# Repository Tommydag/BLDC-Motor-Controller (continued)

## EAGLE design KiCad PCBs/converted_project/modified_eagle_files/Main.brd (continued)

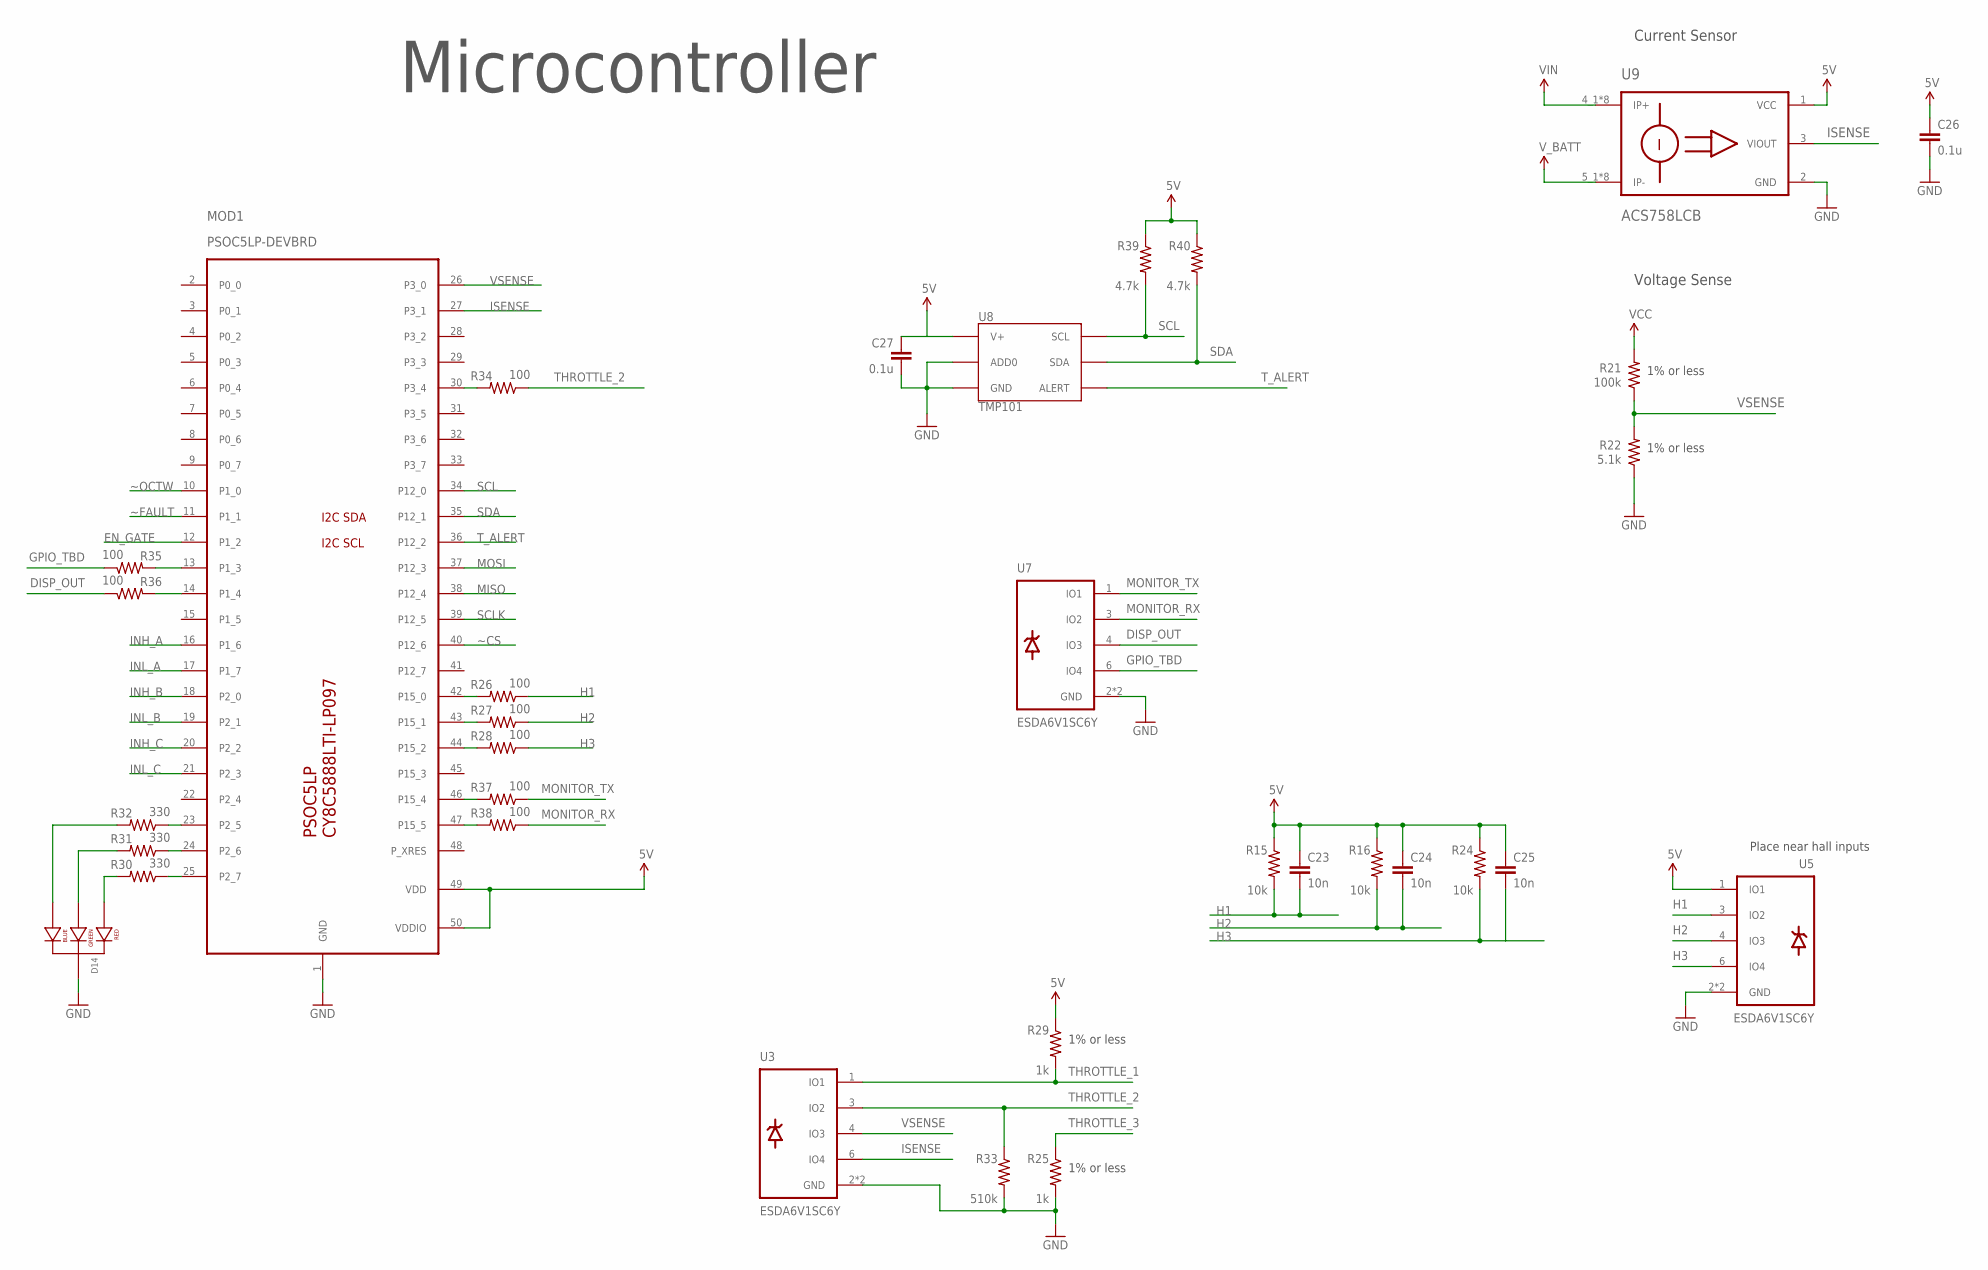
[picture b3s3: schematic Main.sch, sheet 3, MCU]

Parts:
C23, C24, C25: 10n; 0805
C26, C27: 0.1u; 0805
D14: LED-RGB-CC-THRUDIFFUSE; LED-RGB-THRU
MOD1: PSOC5LP-DEVBRD; TQFP100
R15, R16, R24: 10k; 0805
R21: 100k; 1206
R22: 5.1k; 1206
R25, R29: 1k; 0805
R26, R27, R28, R34, R35, R36, R37, R38: 100; 0805
R30, R31, R32: 330; 0805
R33: 510k; 0805
R39, R40: 4.7k; 0805
U3, U5, U7: ESDA6V1SC6Y; SOT23-6
U8: TMP101; SOT23-6
U9: ACS758LCB; CB5PIN

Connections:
5V: C23.1, C24.1, C25.1, C26.1, C27.1, R15.1, R16.1, R24.1, R29.1, R39.1, R40.1, U5.1 (IO1), U8.4 (V+), U9.1 (VCC); also elsewhere on the board
DISP_OUT: R36.1, U7.4 (IO3); also elsewhere on the board
EN_GATE: MOD1.12 (P1_2); also elsewhere on the board
GND: C26.2, C27.2, D14.2 (CATHODE), MOD1.1 (GND), R22.1, R25.2, R33.2, U3.2 (GND), U3.5 (GND), U5.2 (GND), U5.5 (GND), U7.2 (GND), U7.5 (GND), U8.2 (GND), U8.5 (ADD0), U9.2 (GND); also elsewhere on the board
GPIO_TBD: R35.1, U7.6 (IO4); also elsewhere on the board
H1: C23.2, R15.2, R26.1; also elsewhere on the board
H2: C24.2, R16.2, R27.1; also elsewhere on the board
H3: C25.2, R24.2, R28.1; also elsewhere on the board
ISENSE: MOD1.27 (P3_1), U3.6 (IO4), U9.3 (VIOUT)
MONITOR_RX: R38.1, U7.3 (IO2); also elsewhere on the board
MONITOR_TX: R37.1, U7.1 (IO1); also elsewhere on the board
unnamed: MOD1.42 (P15_0), R26.2
unnamed: MOD1.43 (P15_1), R27.2
unnamed: MOD1.44 (P15_2), R28.2
unnamed: MOD1.49 (VDD), MOD1.50 (VDDIO)
unnamed: MOD1.25 (P2_7), R30.1
unnamed: MOD1.24 (P2_6), R31.1
unnamed: MOD1.23 (P2_5), R32.1
unnamed: D14.1 (RED_CATHODE), R30.2
unnamed: D14.3 (GREEN_CATHODE), R31.2
unnamed: D14.4 (BLUE_CATHODE), R32.2
unnamed: MOD1.30 (P3_4), R34.2
unnamed: MOD1.14 (P1_4), R36.2
unnamed: MOD1.13 (P1_3), R35.2
unnamed: MOD1.46 (P15_4), R37.2
unnamed: MOD1.47 (P15_5), R38.2
SCL: MOD1.34 (P12_0), R39.2, U8.1 (SCL)
SDA: MOD1.35 (P12_1), R40.2, U8.6 (SDA)
THROTTLE_1: R29.2, U3.1 (IO1); also elsewhere on the board
THROTTLE_2: R33.1, R34.1, U3.3 (IO2); also elsewhere on the board
THROTTLE_3: R25.1; also elsewhere on the board
T_ALERT: MOD1.36 (P12_2), U8.3 (ALERT)
VCC: R21.2; also elsewhere on the board
VIN: U9.4_1 (IP+), U9.4_2 (IP+), U9.4_3 (IP+), U9.4_4 (IP+), U9.4_5 (IP+), U9.4_6 (IP+), U9.4_7 (IP+), U9.4_8 (IP+); also elsewhere on the board
VSENSE: MOD1.26 (P3_0), R21.1, R22.2, U3.4 (IO3)
V_BATT: U9.5_1 (IP-), U9.5_2 (IP-), U9.5_3 (IP-), U9.5_4 (IP-), U9.5_5 (IP-), U9.5_6 (IP-), U9.5_7 (IP-), U9.5_8 (IP-); also elsewhere on the board

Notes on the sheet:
Microcontroller
Current Sensor
Voltage Sense
Place near hall inputs
1% or less

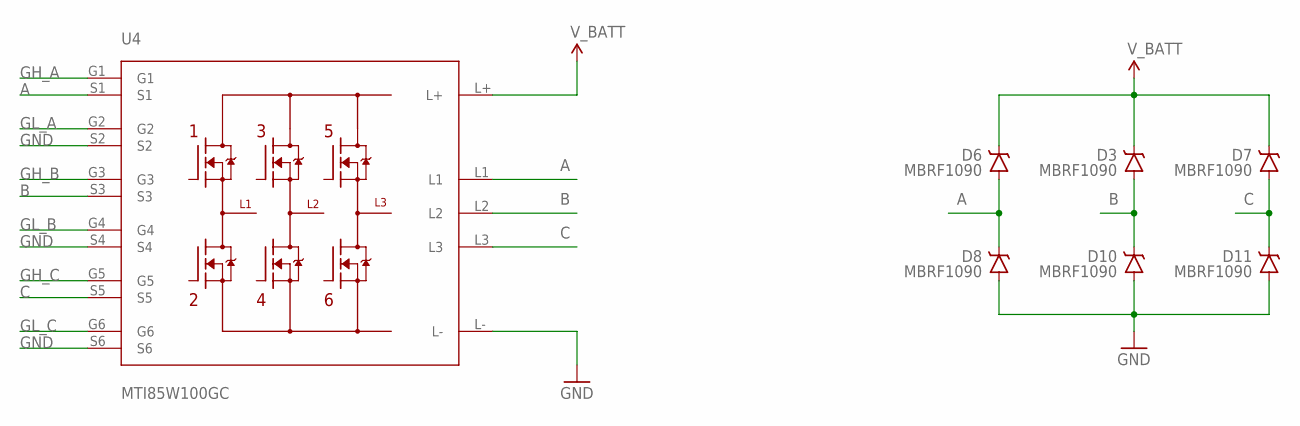
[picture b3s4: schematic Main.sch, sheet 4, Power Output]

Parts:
D3, D6, D7, D8, D10, D11: MBRF1090; TO-220H_2
U4: MTI85W100GC; ISOPLUS-DIL

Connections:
A: D6.2 (A), D8.1 (C), U4.L1, U4.S1; also elsewhere on the board
B: D3.2 (A), D10.1 (C), U4.L2, U4.S3; also elsewhere on the board
C: D7.2 (A), D11.1 (C), U4.L3, U4.S5; also elsewhere on the board
GH_A: U4.G1; also elsewhere on the board
GH_B: U4.G3; also elsewhere on the board
GH_C: U4.G5; also elsewhere on the board
GL_A: U4.G2; also elsewhere on the board
GL_B: U4.G4; also elsewhere on the board
GL_C: U4.G6; also elsewhere on the board
GND: D8.2 (A), D10.2 (A), D11.2 (A), U4.L-, U4.S2, U4.S4, U4.S6; also elsewhere on the board
V_BATT: D3.1 (C), D6.1 (C), D7.1 (C), U4.L+; also elsewhere on the board

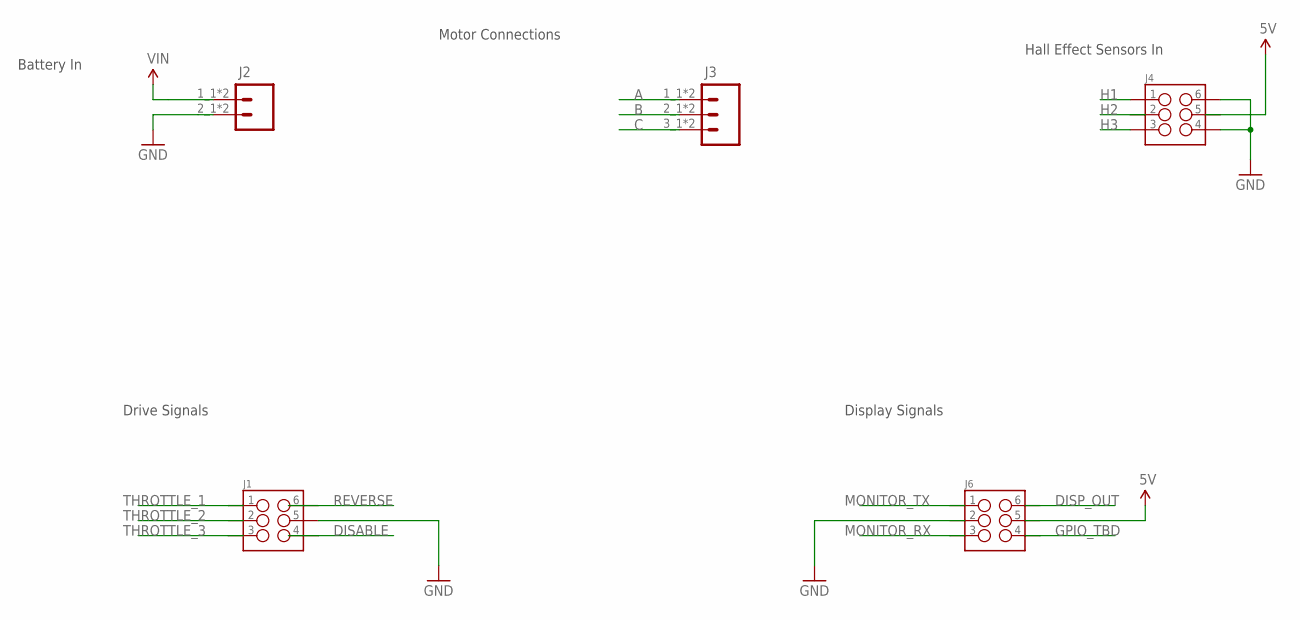
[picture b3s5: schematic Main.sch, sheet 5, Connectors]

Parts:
J1, J4, J6: M03X2MINIFIT_JR; 2X03_MINIFIT_JR
J2: M02MINIFIT-SR; MINIFIT_SR
J3: M03MINIFIT-SR3; MINIFIT-SRX3

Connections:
5V: J4.5, J6.5; also elsewhere on the board
A: J3.1_1 (1), J3.1_2 (1); also elsewhere on the board
B: J3.2_1 (2), J3.2_2 (2); also elsewhere on the board
C: J3.3_1 (3), J3.3_2 (3); also elsewhere on the board
DISABLE: J1.4
DISP_OUT: J6.6; also elsewhere on the board
GND: J2.2_1 (2), J2.2_2 (2), J4.4, J4.6, J6.2; also elsewhere on the board
GPIO_TBD: J6.4; also elsewhere on the board
H1: J4.1; also elsewhere on the board
H2: J4.2; also elsewhere on the board
H3: J4.3; also elsewhere on the board
MONITOR_RX: J6.3; also elsewhere on the board
MONITOR_TX: J6.1; also elsewhere on the board
REVERSE: J1.6
THROTTLE_1: J1.1; also elsewhere on the board
THROTTLE_2: J1.2; also elsewhere on the board
THROTTLE_3: J1.3; also elsewhere on the board
VIN: J2.1_1 (1), J2.1_2 (1); also elsewhere on the board

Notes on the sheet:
Hall Effect Sensors In
Battery In
Drive Signals
Motor Connections
Display Signals

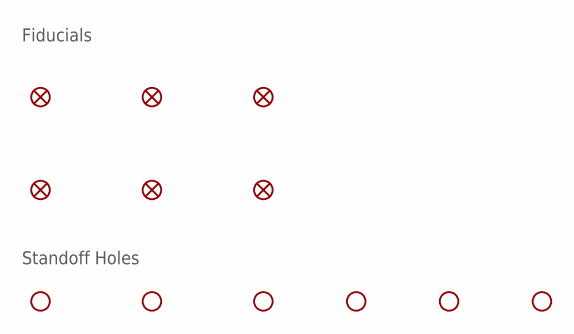
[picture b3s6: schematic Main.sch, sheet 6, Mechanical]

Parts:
FD1, FD2, FD3, FD4, FD5, FD6: FIDUCIAL1X2; FIDUCIAL-1X2
H1, H2, H3, H4, H5, H6: STAND-OFF

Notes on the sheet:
Fiducials
Standoff Holes

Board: 2 copper layers, 112 parts (0 on the bottom side), 83 nets, no tracks yet.

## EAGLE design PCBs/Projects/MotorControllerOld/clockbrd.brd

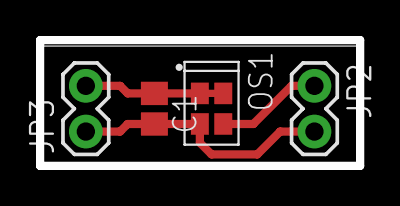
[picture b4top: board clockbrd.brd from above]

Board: 2 copper layers, 17.8 x 7.0 mm, 5 parts (0 on the bottom side), 3 nets.

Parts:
C1: C0805
DRILEGEND: DRILEGEND
JP2, JP3: 1X02
OS1: OSC-OE-IQXO-793; 2.5X2-4-PAD

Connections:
CLK: JP2.1, OS1.3
GND: C1.2, JP2.2, JP3.1, OS1.2
VCC: C1.1, JP3.2, OS1.1, OS1.4

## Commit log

2016-12-05 Initial Commit -Added Progress as of now
2016-12-06 Start of main motor controller -See main.sch -Cleaned up some library issues with previously made parts
2016-12-06 Adding Library Files
2016-12-09 Added Board file for gate driver board
2016-12-16 RepoFix
2016-12-16 Added Parts, work on power input protection
2016-12-16 Finished input protection sheet
2016-12-16 gate driver halfway cleaned up
2016-12-16 Gate driver completed
2016-12-16 Added power fet part and start of psoc5lp part -further schematic cleaning done on the gate driver -datasheet for some of the new parts have been added
2016-12-16 Freewheeling diodes selected and mcu created -documentation for fet module corrected -minor symbol changes
2016-12-16 Updates to schematics
2016-12-21 prj file
2017-01-06 Added software to project repo -Workspace contains a testing project and a sample sensored bldc controller from cypress
2017-01-16 Major updates to connectors -ESD protection almost complete -TODOs: Packages for fet module, current sensor. -TODOs: Verify correct resistor/cap packages
2017-01-19 Preparing for move to kiCad
2017-01-22 Converted project to Kicad since autodesk took over eagle -I cant get the board size needed using eagle even with premium -cleanup still required
2017-01-23 Fix to modules
2017-01-23 Schematic in eagle finished -decided to stick with eagle for the time being since the kicad switchover would take a lot of time -freewheeling diodes switched to vertical packages -footprint for psoc 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
2017-01-23 PCB layout progress -completed first revision of input protection -added drc file which added 2 more layers and modified parameters of sparkfun's stock DRC -corrected schematic error which listed lab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
2017-01-23 More work done on the buck converter of the drv8301
2017-01-23 Finished gate driver layout -added the design rules check file that was omitted in a previous commit
2017-01-24 Lots more layout complete -major micro controller rewiring -removed a connector and replaced it with a header -added some datasheets for cykit
2017-01-24 First pass layout complete -still need to go over it with a fine toothed comb
2017-01-24 fixed a couple airwires -Added keepout below 1206 resistors -TODO: current path from power input to fets needs to bet larger -TODO: silk screen fixes -TODO: DRV8301 solder mask fix -TODO: Mounting ho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
2017-01-24 Fixed current path concerns -Arranged top fiducials
2017-01-25 Lots of fine detail work -Mounting holes placed -Silk fixes and additions -SEM added to board
2017-01-25 Laundry list of fixes -Changed feedback point for buck convert -Labeled layers in copper -Added filter cap to current sense line -Fixed footprint of acs758
2017-01-25 Footprint updates and drc fixes -Additionally, filter cap added to throttle
2017-01-26 RevA board sent to board house -lots of little silkscreen additions -tmp101 datasheet added -CAM files saved
2017-01-28 Removed Kicad folder from repo -Removed since because eagle was kept instead of transitioning
2017-01-28 Added gitignore files to make repo and commits easier
2017-01-28 Fixed gitignore
2017-01-28 fixed untracked files
2017-01-29 Added pdfs of RevB schematic and pcb -Cleaned schematic of RevB
2017-01-30 Work on DRV8301 communication over SPI -Lots of additions in the topdesign that need to be fleshed out in the future
2017-01-30 Added BOM to cam files
2017-01-31 BOM REV1 for PCB REVB
2017-02-01 Added digikey friendly BOM -Added PurchaseOrders.7z which includes receipts from purchases made -PurchaseOrders.7z is currently encrypted until I have the time to remove personal data from pdfs
2017-02-10 Added drv8301_utilities.c
2017-02-18 Lots of software work, a datasheet update -Motor now running on revB board
2017-02-18 More playing around with throttle settings
2017-02-27 Starting work on Rev C, Rev B has been abandoned but not forgotten -Adding datasheets of some the the parts rec C will utilize -Added some power supply calculations -Added LT3045 and LT8631 parts in 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
2017-02-28 Gate driver circuitry added, many schematic updates -Some parts and datasheets also added
2017-03-02 Bulk of schematic work finished, beginning layout
2017-03-02 Added test points to schematic -Restarted board
2017-03-02 switching psu layout 50% done
2017-03-02 LDO placed and routed
2017-03-03 Major layout work
2017-03-03 More signals run
2017-03-03 Most Layout complete
2017-03-03 Board mostly completed
2017-03-04 All DRC errors fixed, labels applied, teardrop ULP run
2017-03-10 Board Tag
2017-03-16 Commiting the changes made in revC -Some documents related to revC design have also be included -some datasheets still missing
